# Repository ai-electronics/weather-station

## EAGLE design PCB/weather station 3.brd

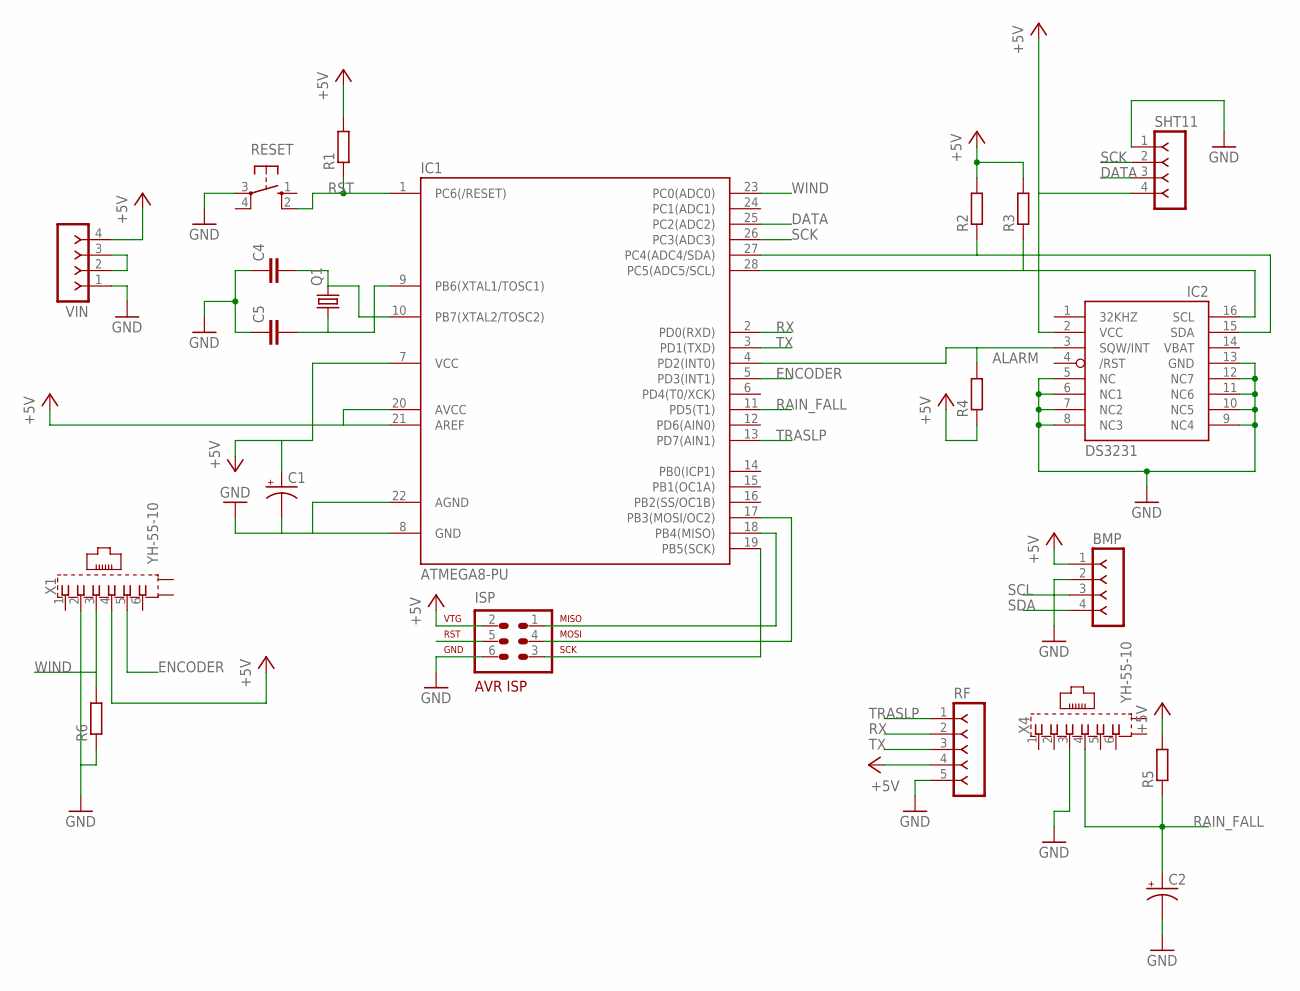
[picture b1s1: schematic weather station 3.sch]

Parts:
BMP: F-1X04-SIP-100-40; SIP-100-04-40
C1, C2: 10UF-25V-20%(PTH); CPOL-RADIAL-10UF-25V
C4, C5: C-EU025-024X044; C025-024X044
IC1: ATMEGA8-PU; DIL28-3
IC2: DS3231/SO; SO16W
ISP: AVR-ISP-6
Q1: CRYSTALHC49S; HC49/S
R1, R2, R3, R4, R5, R6: R-EU_0204/7; 0204/7
RESET: 10-XX; B3F-10XX
RF: F-1X05-SIP-100-40; SIP-100-05-40
SHT11: F-1X04-SIP-100-40; SIP-100-04-40
VIN: F-1X04-SIP-100-40Y; SIP-100-04-40Y
X1, X4: YH-55-10

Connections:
+5V: BMP.1, C1.1 (+), IC1.7 (VCC), IC1.20 (AVCC), IC1.21 (AREF), IC2.2 (VCC), ISP.2, R1.2, R2.2, R3.2, R4.1, R5.2, RF.4, SHT11.4, VIN.4, X1.4
ALARM: IC1.4 (PD2(INT0)), IC2.3 (SQW/INT), R4.2
DATA: IC1.25 (PC2(ADC2)), SHT11.3
ENCODER: IC1.5 (PD3(INT1)), X1.5
GND: BMP.2, C1.2 (-), C2.2 (-), C4.1, C5.1, IC1.8 (GND), IC1.22 (AGND), IC2.5 (NC), IC2.6 (NC1), IC2.7 (NC2), IC2.8 (NC3), IC2.9 (NC4), IC2.10 (NC5), IC2.11 (NC6), IC2.12 (NC7), IC2.13 (GND), ISP.6, R6.1, RESET.3, RF.5, SHT11.1, VIN.1, X1.2, X4.3
unnamed: VIN.2, VIN.3
unnamed: IC1.18 (PB4(MISO)), ISP.1
unnamed: C4.2, IC1.10 (PB7(XTAL2/TOSC2)), Q1.2
unnamed: C5.2, IC1.9 (PB6(XTAL1/TOSC1)), Q1.1
unnamed: IC1.19 (PB5(SCK)), ISP.3
unnamed: IC1.17 (PB3(MOSI/OC2)), ISP.4
RAIN_FALL: C2.1 (+), IC1.11 (PD5(T1)), R5.1, X4.4
RST: IC1.1 (PC6(/RESET)), ISP.5, R1.1, RESET.2 (S1)
RX: IC1.2 (PD0(RXD)), RF.2
SCK: IC1.26 (PC3(ADC3)), SHT11.2
SCL: BMP.3, IC1.28 (PC5(ADC5/SCL)), IC2.16 (SCL), R3.1
SDA: BMP.4, IC1.27 (PC4(ADC4/SDA)), IC2.15 (SDA), R2.1
TRASLP: IC1.13 (PD7(AIN1)), RF.1
TX: IC1.3 (PD1(TXD)), RF.3
VBAT: IC2.14 (VBAT)
WIND: IC1.23 (PC0(ADC0)), R6.2, X1.3

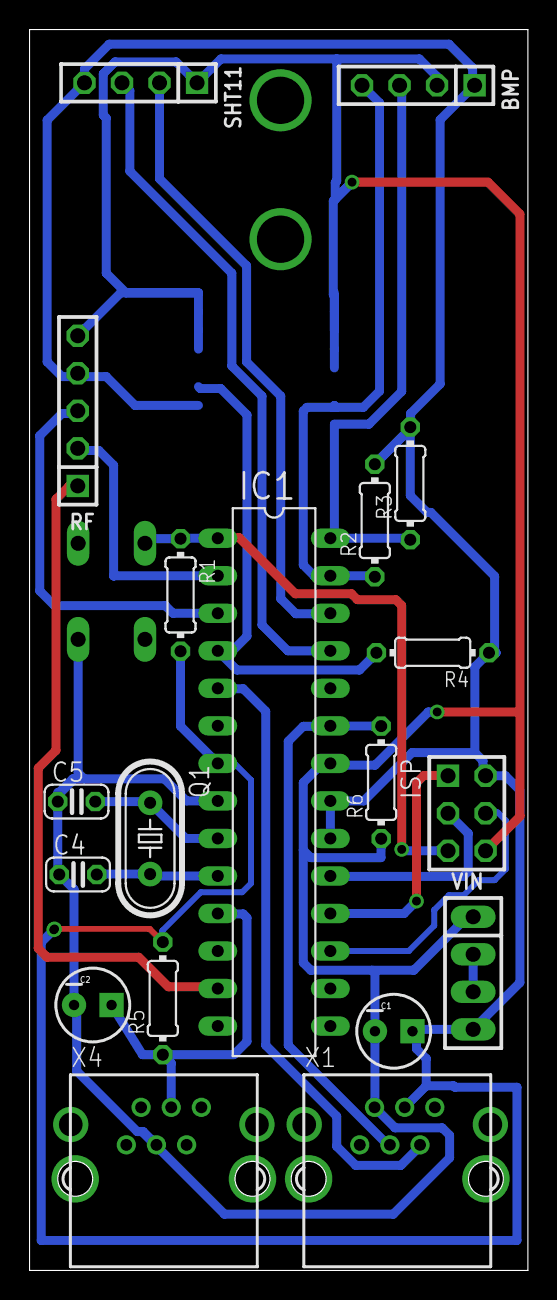
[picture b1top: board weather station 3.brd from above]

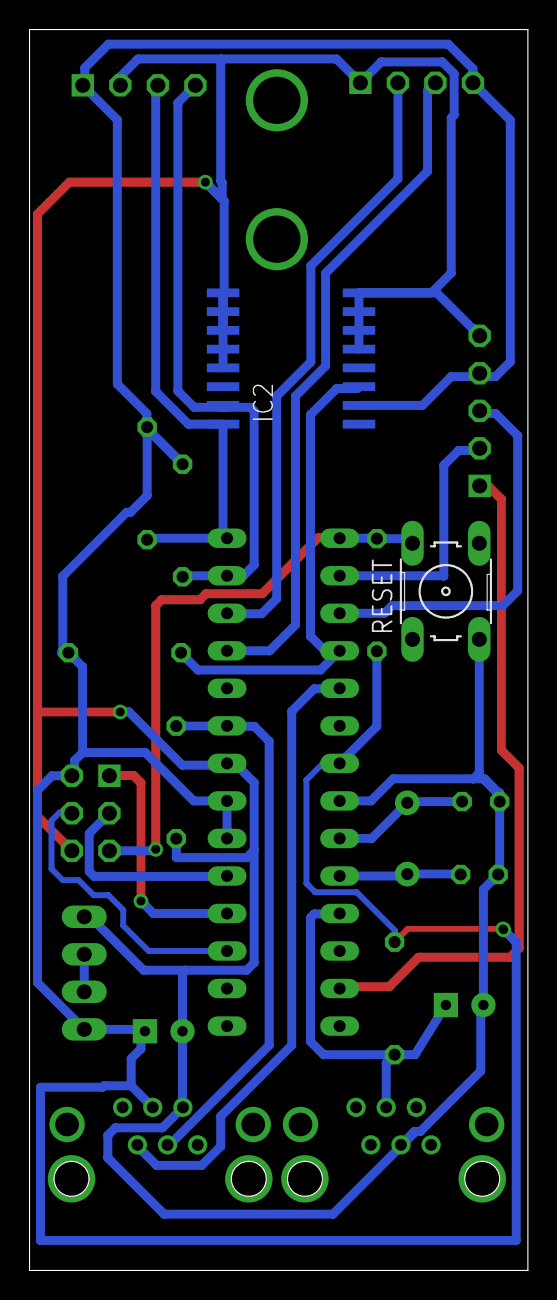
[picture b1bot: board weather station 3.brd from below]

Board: 2 copper layers, 33.7 x 84.0 mm, 21 parts (2 on the bottom side), 20 nets.

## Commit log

2017-09-25 Create awaln
2017-09-25 Create awalan

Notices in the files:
parts and their libraries:
con-headers-jp: Copyright (C) 2008, Bob Starr
SparkFun-Capacitors: Licensing: Creative Commons ShareAlike 4.0 International - https://creativecommons.org/licenses/by-sa/4.0
